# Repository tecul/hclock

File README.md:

# hclock
this is a low cost alarm clock

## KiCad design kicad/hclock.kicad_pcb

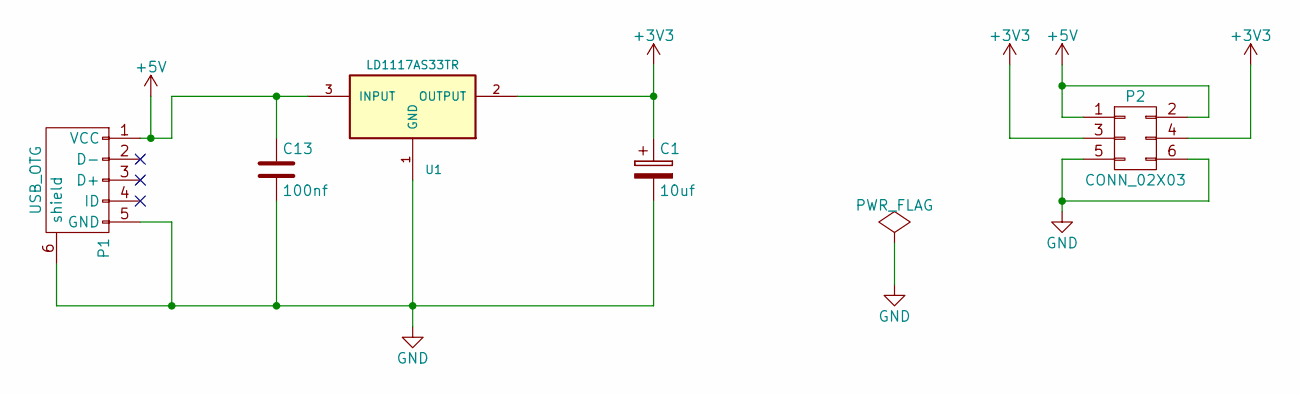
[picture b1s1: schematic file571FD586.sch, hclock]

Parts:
C1: 10uf; C1V8
C13: 100nf; C_0805_HandSoldering
P1: USB_OTG; USB_Mini-B
P2: CONN_02X03; Pin_Header_Straight_2x03
U1: LD1117AS33TR; SOT-223

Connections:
+3V3: C1.1, P2.3, P2.4, U1.2 (OUTPUT); also elsewhere on the board
+5V: C13.1, P1.1 (VCC), P2.1, P2.2, U1.3 (INPUT); also elsewhere on the board
GND: C1.2, C13.2, P1.5 (GND), P1.6 (shield), P2.5, P2.6, U1.1 (GND); also elsewhere on the board

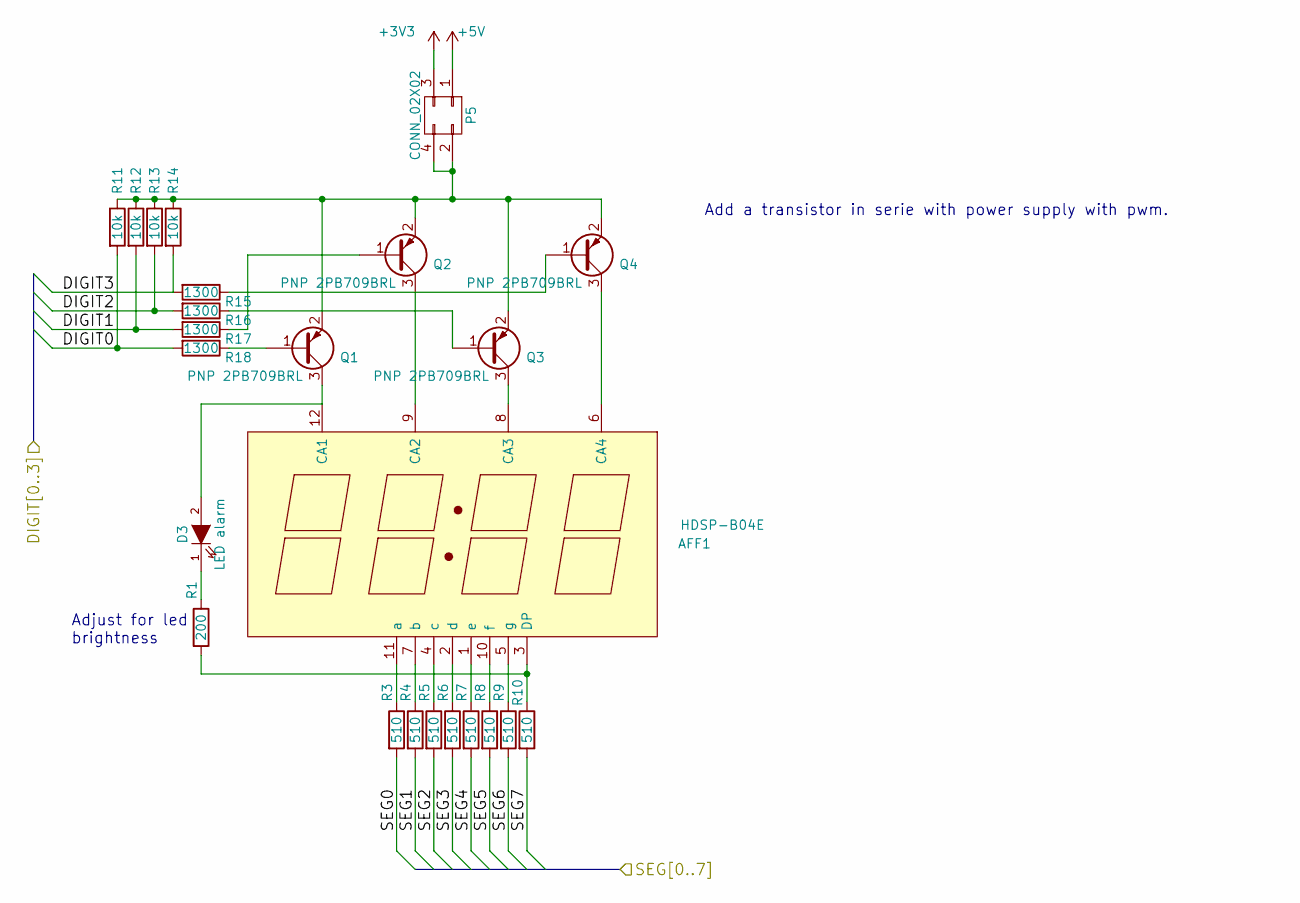
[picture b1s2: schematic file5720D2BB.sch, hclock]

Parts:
AFF1: HDSP-B04E; hdsp-b04e
D3: LED alarm; LED-3MM
P5: CONN_02X02; Pin_Header_Straight_2x02
Q1, Q2, Q3, Q4: PNP 2PB709BRL; SOT-23_Handsoldering
R1: 200; R_0805_HandSoldering
R3, R4, R5, R6, R7, R8, R9, R10: 510; R_0805_HandSoldering
R11, R12, R13, R14: 10k; R_0805_HandSoldering
R15, R16, R17, R18: 1300; R_0805_HandSoldering

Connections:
+3V3: P5.3; also elsewhere on the board
+5V: P5.1; also elsewhere on the board
/display/DIGIT0: R11.2, R18.2; also elsewhere on the board
/display/DIGIT1: R12.2, R17.2; also elsewhere on the board
/display/DIGIT2: R13.2, R16.2; also elsewhere on the board
/display/DIGIT3: R14.2, R15.2; also elsewhere on the board
/display/SEG0: R3.2; also elsewhere on the board
/display/SEG1: R4.2; also elsewhere on the board
/display/SEG2: R5.2; also elsewhere on the board
/display/SEG3: R6.2; also elsewhere on the board
/display/SEG4: R7.2; also elsewhere on the board
/display/SEG5: R8.2; also elsewhere on the board
/display/SEG6: R9.2; also elsewhere on the board
/display/SEG7: R10.2; also elsewhere on the board
unnamed: AFF1.1 (e), R7.1
unnamed: AFF1.2 (d), R6.1
unnamed: AFF1.3 (DP), R1.2, R10.1
unnamed: AFF1.4 (c), R5.1
unnamed: AFF1.5 (g), R9.1
unnamed: AFF1.6 (CA4), Q4.3 (C)
unnamed: AFF1.7 (b), R4.1
unnamed: AFF1.8 (CA3), Q3.3 (C)
unnamed: AFF1.9 (CA2), Q2.3 (C)
unnamed: AFF1.10 (f), R8.1
unnamed: AFF1.11 (a), R3.1
unnamed: AFF1.12 (CA1), D3.2 (A), Q1.3 (C)
unnamed: D3.1 (K), R1.1
unnamed: P5.2, P5.4, Q1.2 (E), Q2.2 (E), Q3.2 (E), Q4.2 (E), R11.1, R12.1, R13.1, R14.1
unnamed: Q1.1 (B), R18.1
unnamed: Q2.1 (B), R17.1
unnamed: Q3.1 (B), R16.1
unnamed: Q4.1 (B), R15.1

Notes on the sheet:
Add a transistor in serie with power supply with pwm.
Adjust for led brightness

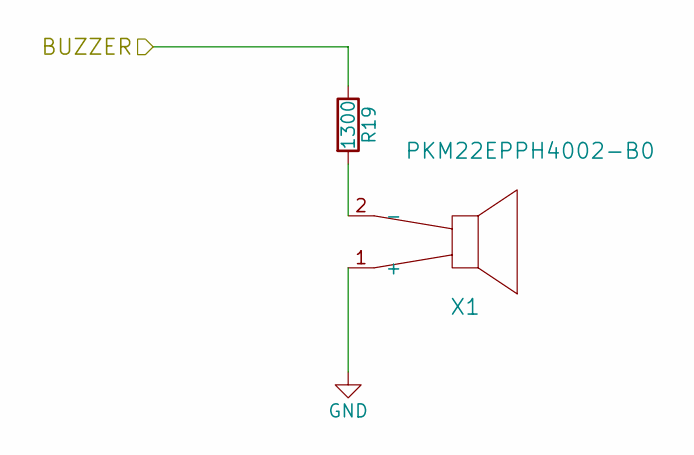
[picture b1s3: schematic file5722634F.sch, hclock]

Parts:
R19: 1300; R_0805_HandSoldering
X1: PKM22EPPH4002-B0; BUZZER

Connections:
/buzzer/BUZZER: R19.1; also elsewhere on the board
GND: X1.1 (+); also elsewhere on the board
unnamed: R19.2, X1.2 (-)

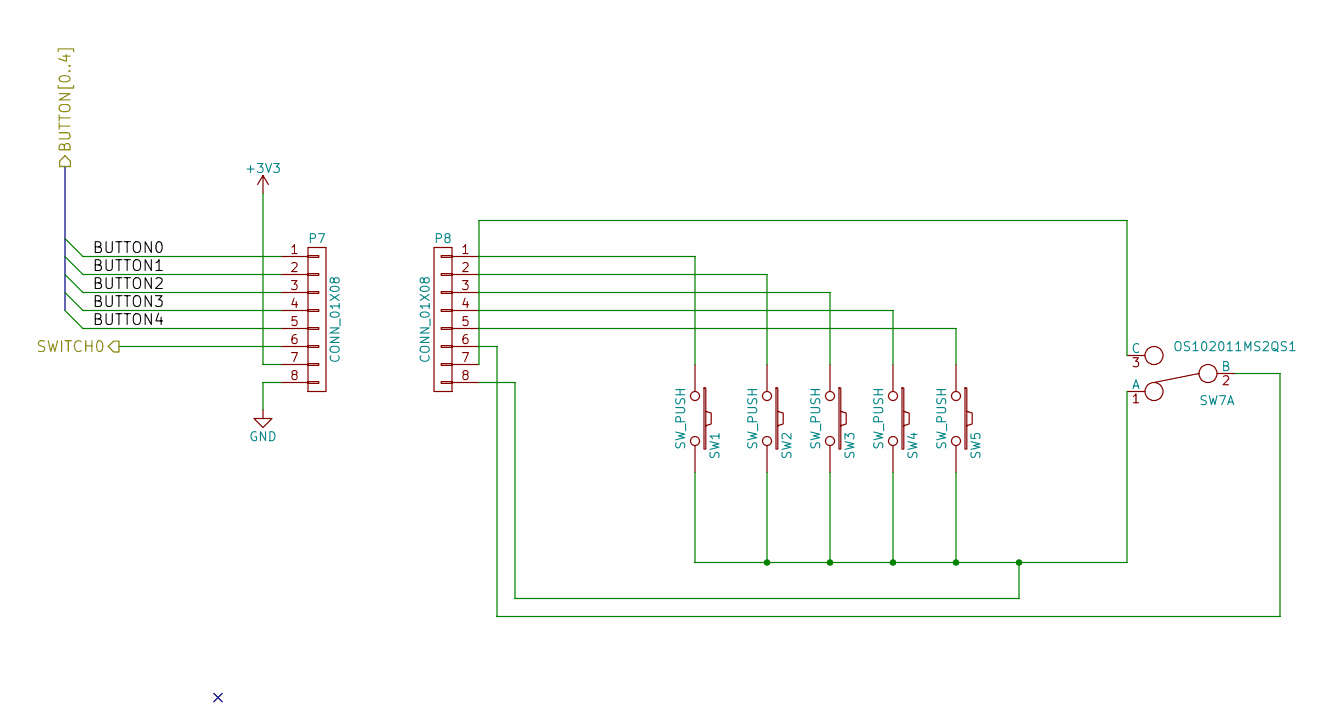
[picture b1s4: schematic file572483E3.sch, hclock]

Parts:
P7, P8: CONN_01X08; Pin_Header_Straight_1x08
SW1, SW2, SW3, SW4, SW5: SW_PUSH; SW_PUSH_SMALL
SW7: OS102011MS2QS1

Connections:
+3V3: P7.7; also elsewhere on the board
/button/BUTTON0: P7.1; also elsewhere on the board
/button/BUTTON1: P7.2; also elsewhere on the board
/button/BUTTON2: P7.3; also elsewhere on the board
/button/BUTTON3: P7.4; also elsewhere on the board
/button/BUTTON4: P7.5; also elsewhere on the board
/button/SWITCH0: P7.6; also elsewhere on the board
GND: P7.8; also elsewhere on the board
unnamed: P8.1, SW1.1
unnamed: P8.2, SW2.1
unnamed: P8.3, SW3.1
unnamed: P8.4, SW4.1
unnamed: P8.5, SW5.1
unnamed: P8.6, SW7.2 (B)
unnamed: P8.7, SW7.3 (C)
unnamed: P8.8, SW1.2, SW2.2, SW3.2, SW4.2, SW5.2, SW7.1 (A)

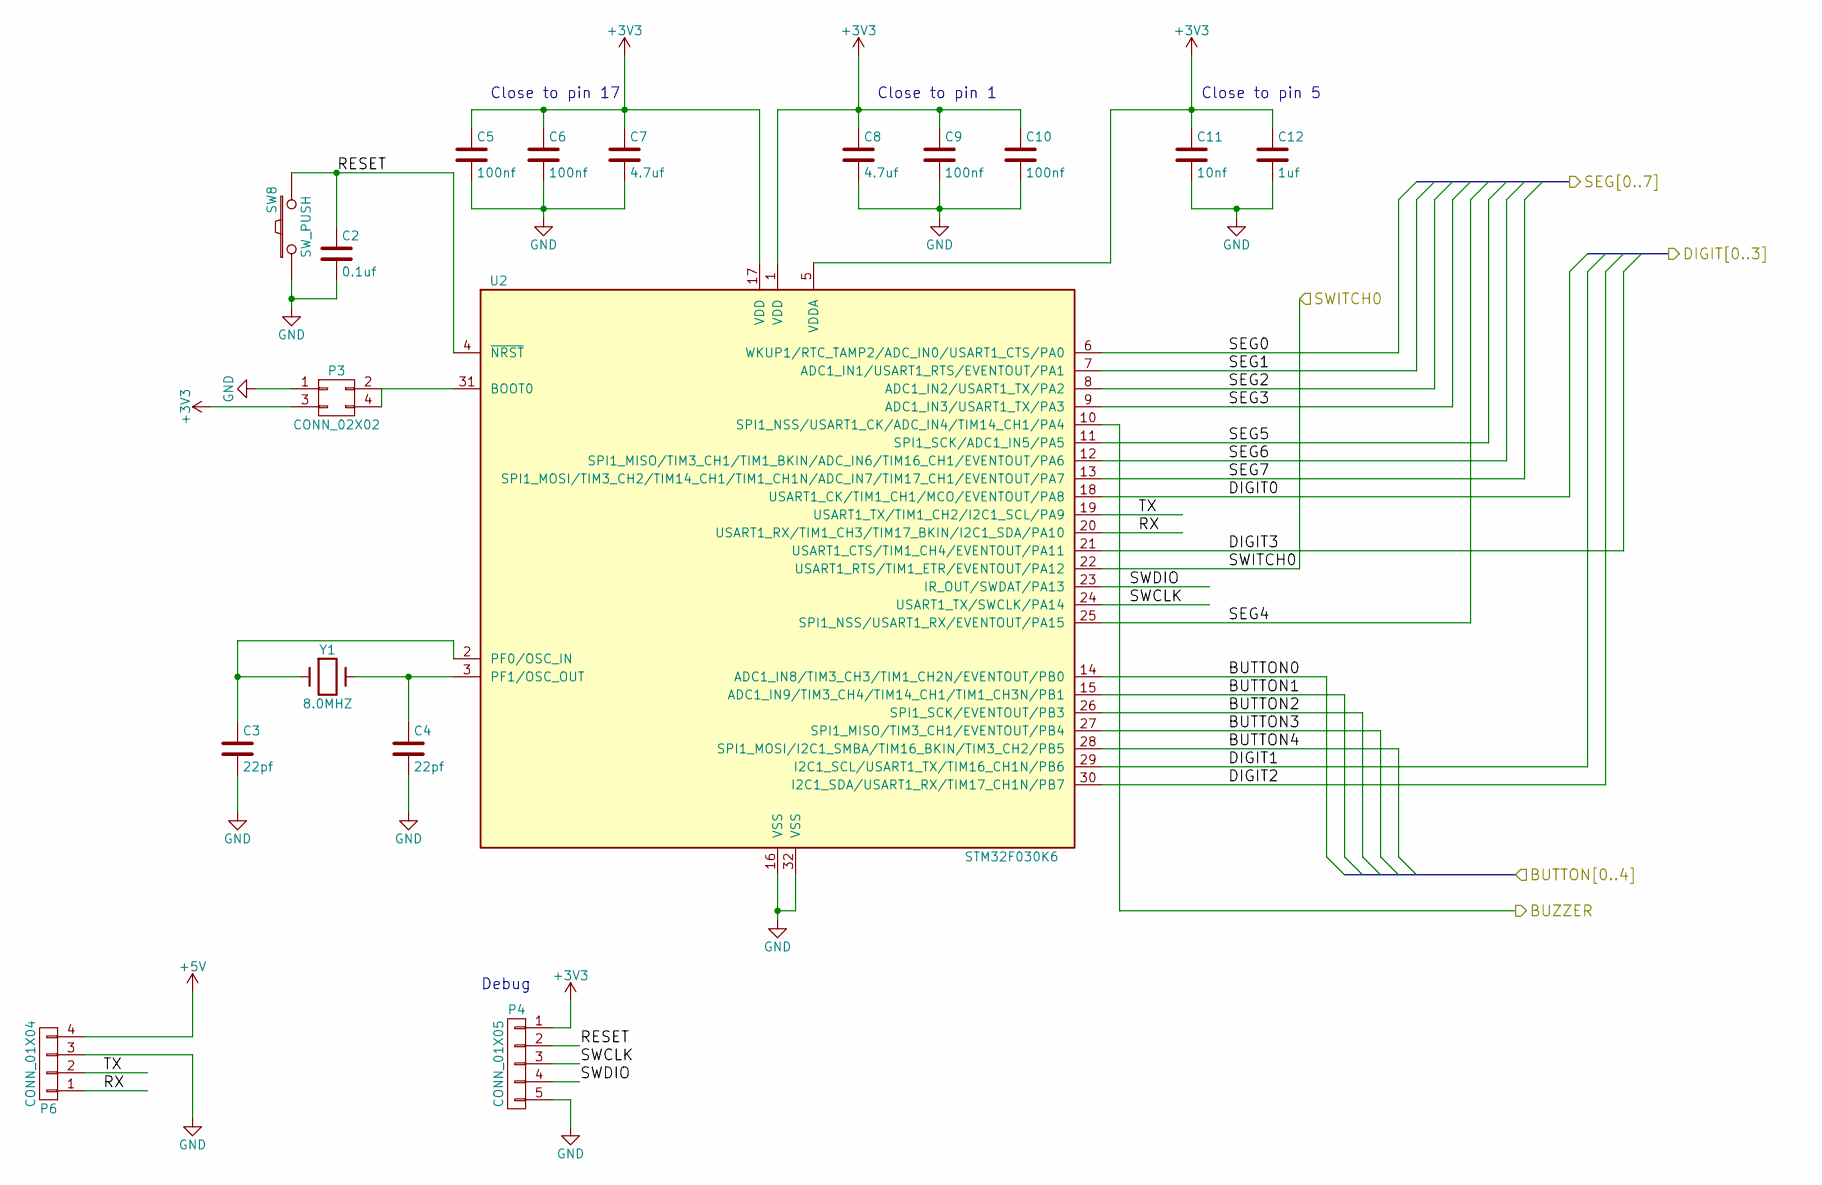
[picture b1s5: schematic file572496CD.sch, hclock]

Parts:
C2: 0.1uf; C_0805_HandSoldering
C3, C4: 22pf; C_0805_HandSoldering
C5, C6, C9, C10: 100nf; C_0805_HandSoldering
C7, C8: 4.7uf; C_0805_HandSoldering
C11: 10nf; C_0805_HandSoldering
C12: 1uf; C_0805_HandSoldering
P3: CONN_02X02; Pin_Header_Straight_2x02
P4: CONN_01X05; Pin_Header_Straight_1x05
P6: CONN_01X04; Pin_Header_Straight_1x04
SW8: SW_PUSH; SW_PUSH_SMALL
U2: STM32F030K6; LQFP-32_7x7mm_Pitch0.8mm
Y1: 8.0MHZ; Crystal_HC49-U_Vertical

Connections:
+3V3: C5.1, C6.1, C7.1, C8.1, C9.1, C10.1, C11.1, C12.1, P3.3, P4.1, U2.1 (VDD), U2.5 (VDDA), U2.17 (VDD); also elsewhere on the board
+5V: P6.4; also elsewhere on the board
/button/BUTTON0: U2.14 (ADC1_IN8/TIM3_CH3/TIM1_CH2N/EVENTOUT/PB0); also elsewhere on the board
/button/BUTTON1: U2.15 (ADC1_IN9/TIM3_CH4/TIM14_CH1/TIM1_CH3N/P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); also elsewhere on the board
/button/BUTTON2: U2.26 (SPI1_SCK/EVENTOUT/PB3); also elsewhere on the board
/button/BUTTON3: U2.27 (SPI1_MISO/TIM3_CH1/EVENTOUT/PB4); also elsewhere on the board
/button/BUTTON4: U2.28 (SPI1_MOSI/I2C1_SMBA/TIM16_BKIN/TIM3_CH2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); also elsewhere on the board
/button/SWITCH0: U2.22 (USART1_RTS/TIM1_ETR/EVENTOUT/PA12); also elsewhere on the board
/buzzer/BUZZER: U2.10 (SPI1_NSS/USART1_CK/ADC_IN4/TIM14_CH1/PA4); also elsewhere on the board
/display/DIGIT0: U2.18 (USART1_CK/TIM1_CH1/MCO/EVENTOUT/PA8); also elsewhere on the board
/display/DIGIT1: U2.29 (I2C1_SCL/USART1_TX/TIM16_CH1N/PB6); also elsewhere on the board
/display/DIGIT2: U2.30 (I2C1_SDA/USART1_RX/TIM17_CH1N/PB7); also elsewhere on the board
/display/DIGIT3: U2.21 (USART1_CTS/TIM1_CH4/EVENTOUT/PA11); also elsewhere on the board
/display/SEG0: U2.6 (WKUP1/RTC_TAMP2/ADC_IN0/USART1_CTS/PA0); also elsewhere on the board
/display/SEG1: U2.7 (ADC1_IN1/USART1_RTS/EVENTOUT/PA1); also elsewhere on the board
/display/SEG2: U2.8 (ADC1_IN2/USART1_TX/PA2); also elsewhere on the board
/display/SEG3: U2.9 (ADC1_IN3/USART1_TX/PA3); also elsewhere on the board
/display/SEG4: U2.25 (SPI1_NSS/USART1_RX/EVENTOUT/PA15); also elsewhere on the board
/display/SEG5: U2.11 (SPI1_SCK/ADC1_IN5/PA5); also elsewhere on the board
/display/SEG6: U2.12 (SPI1_MISO/TIM3_CH1/TIM1_BKIN/ADC_IN6/TI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); also elsewhere on the board
/display/SEG7: U2.13 (SPI1_MOSI/TIM3_CH2/TIM14_CH1/TIM1_CH1N/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); also elsewhere on the board
/micro/RESET: C2.1, P4.2, SW8.2, U2.4 (~NRST)
/micro/RX: P6.1, U2.20 (USART1_RX/TIM1_CH3/TIM17_BKIN/I2C1_SDA/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)
/micro/SWCLK: P4.3, U2.24 (USART1_TX/SWCLK/PA14)
/micro/SWDIO: P4.4, U2.23 (IR_OUT/SWDAT/PA13)
/micro/TX: P6.2, U2.19 (USART1_TX/TIM1_CH2/I2C1_SCL/PA9)
GND: C2.2, C3.2, C4.2, C5.2, C6.2, C7.2, C8.2, C9.2, C10.2, C11.2, C12.2, P3.1, P4.5, P6.3, SW8.1, U2.16 (VSS), U2.32 (VSS); also elsewhere on the board
unnamed: C3.1, U2.2 (PF0/OSC_IN), Y1.1
unnamed: C4.1, U2.3 (PF1/OSC_OUT), Y1.2
unnamed: P3.2, P3.4, U2.31 (BOOT0)

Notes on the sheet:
Close to pin 17
Close to pin 1
Close to pin 5
Debug

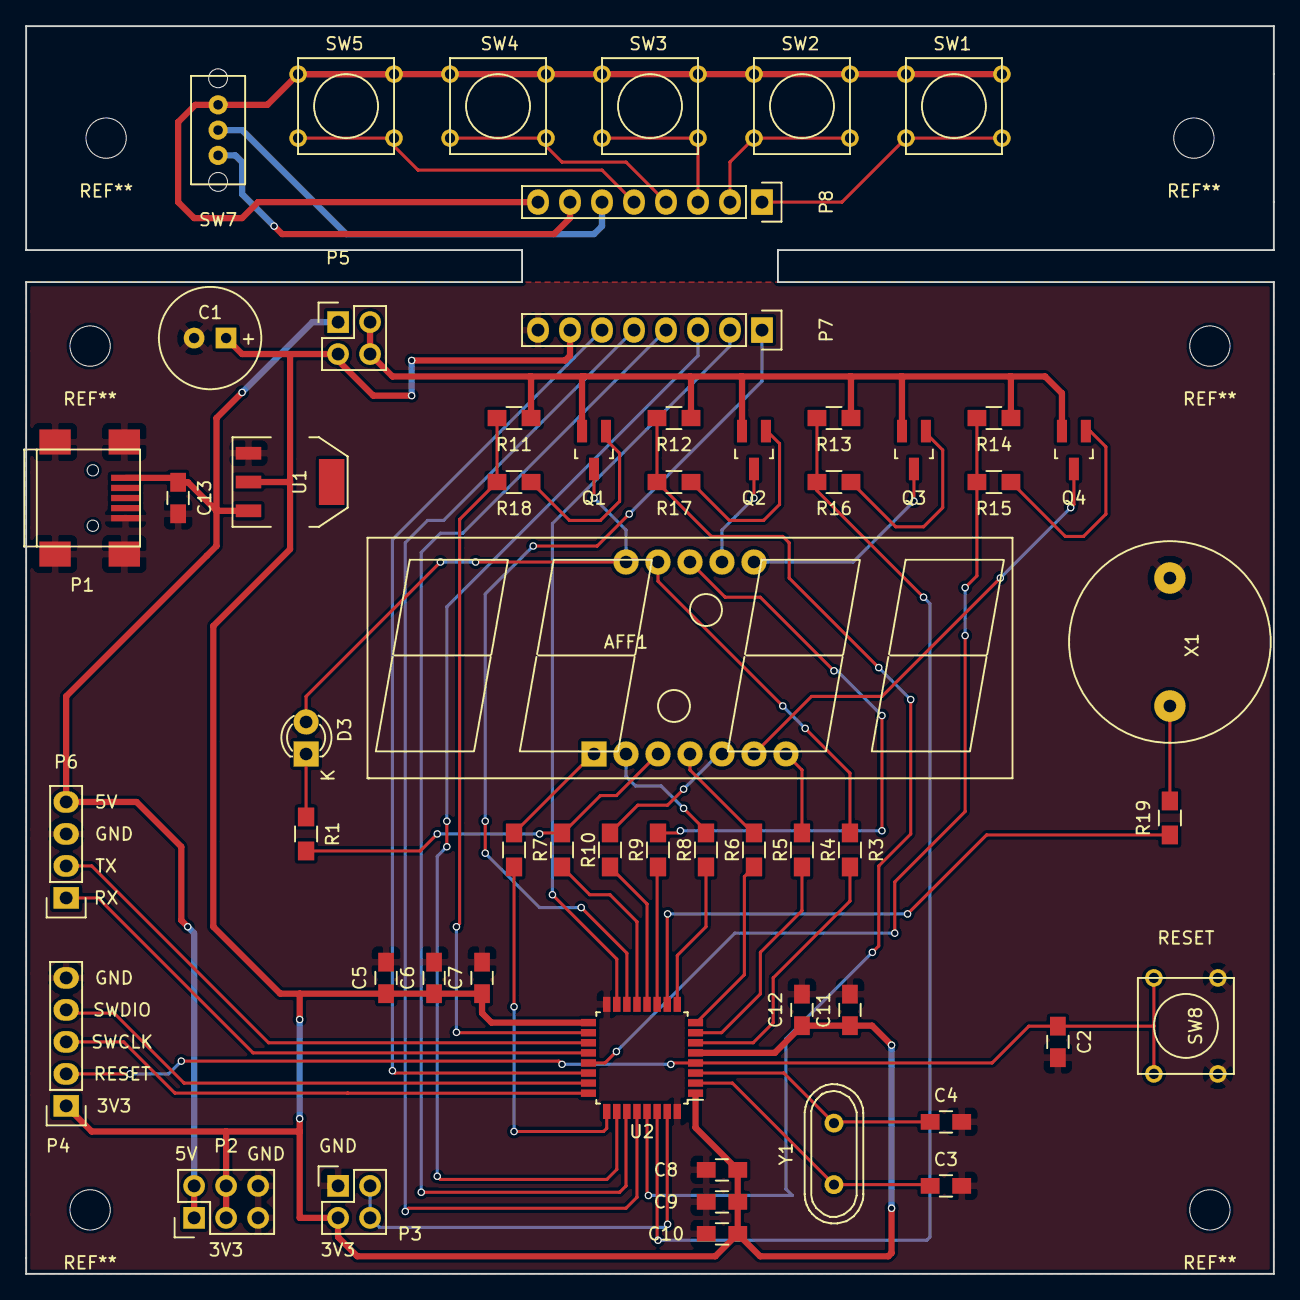
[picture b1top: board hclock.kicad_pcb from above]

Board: 2 copper layers, 99.1 x 99.1 mm, 56 parts (0 on the bottom side), 57 nets.

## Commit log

2016-07-23 initial revision
